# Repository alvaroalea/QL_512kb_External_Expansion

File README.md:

# SINCLAIR QL 512kB External Rom Expansion

(C) 2022 Alvaro Alea Fernandez

License under: CERN Open Hardware Licence Version 2 - Strongly Reciprocal

https://ohwr.org/cern_ohl_s_v2.txt

This is based on the work of McLeod Ideafix, Jose Leandro, Zerover and tcat between others. 

This board will provide up to 512kB aditional of static RAM (fast-ram) to the sinclair QL.

Two board can be stacked to got a maximun of 898Kb of Memory. (same as Miracle's Trump Card)

Be aware you can not have 2 memory expansion in same area (Jose Leandro's QBide, Trump Card, etc...)

Provide a expansion conector to allow conect aditional interfaces.

There area available 4 configuration trough solder jumpers in the PCB.
* 512kB - This is the standar 512kB expansion for any QL
* 256kB - This is for use as a second expansion, use the full QL space for a maximun of 898kB, be aware that this is incompatible with a lot of expansion card, so use with caution (Any expansion card that do not use jumper for configuration will be incompatible).
* 192kB - Similar to 256kB provide aditional space for expansion cards correctly configured.
* 128kB - Similar to 256kB provide aditional space for expansion cards correctly configured.

Be aware that the configuration of 128Kb can not be installed alone.
For be able to use 128kB, for a total of 768kB, is mandatory to have an aditional expansion card that put ROM in address E00000h, in other case the QL ROM will hang indicating RAM malfunction, because a weired overlap of the internal 128kB with this external 128kB.

https://www.instagram.com/p/CZWfWcUM5mx/

In the GAL folder there is the source code to be compiled with GALasm that you can found here: https://github.com/daveho/GALasm

## Mini Trump Card Compatibility

I have done a version of the trump card disk interface here: https://github.com/alvaroalea/QL_MiniTrump3 , this interface do not
provide memory like the original one. You can combine two of this card and the minitrump to got the same of the original trump card.

You should conect the 512Kb Card to the QL, the MiniTrump Card to the 512Kb, and the +256Kb card to the Mini Trump, and in this board
yo need to change the solder jumper (JP1) to 2-3 to allow the Minitrump card to coordinate with the second memory card.

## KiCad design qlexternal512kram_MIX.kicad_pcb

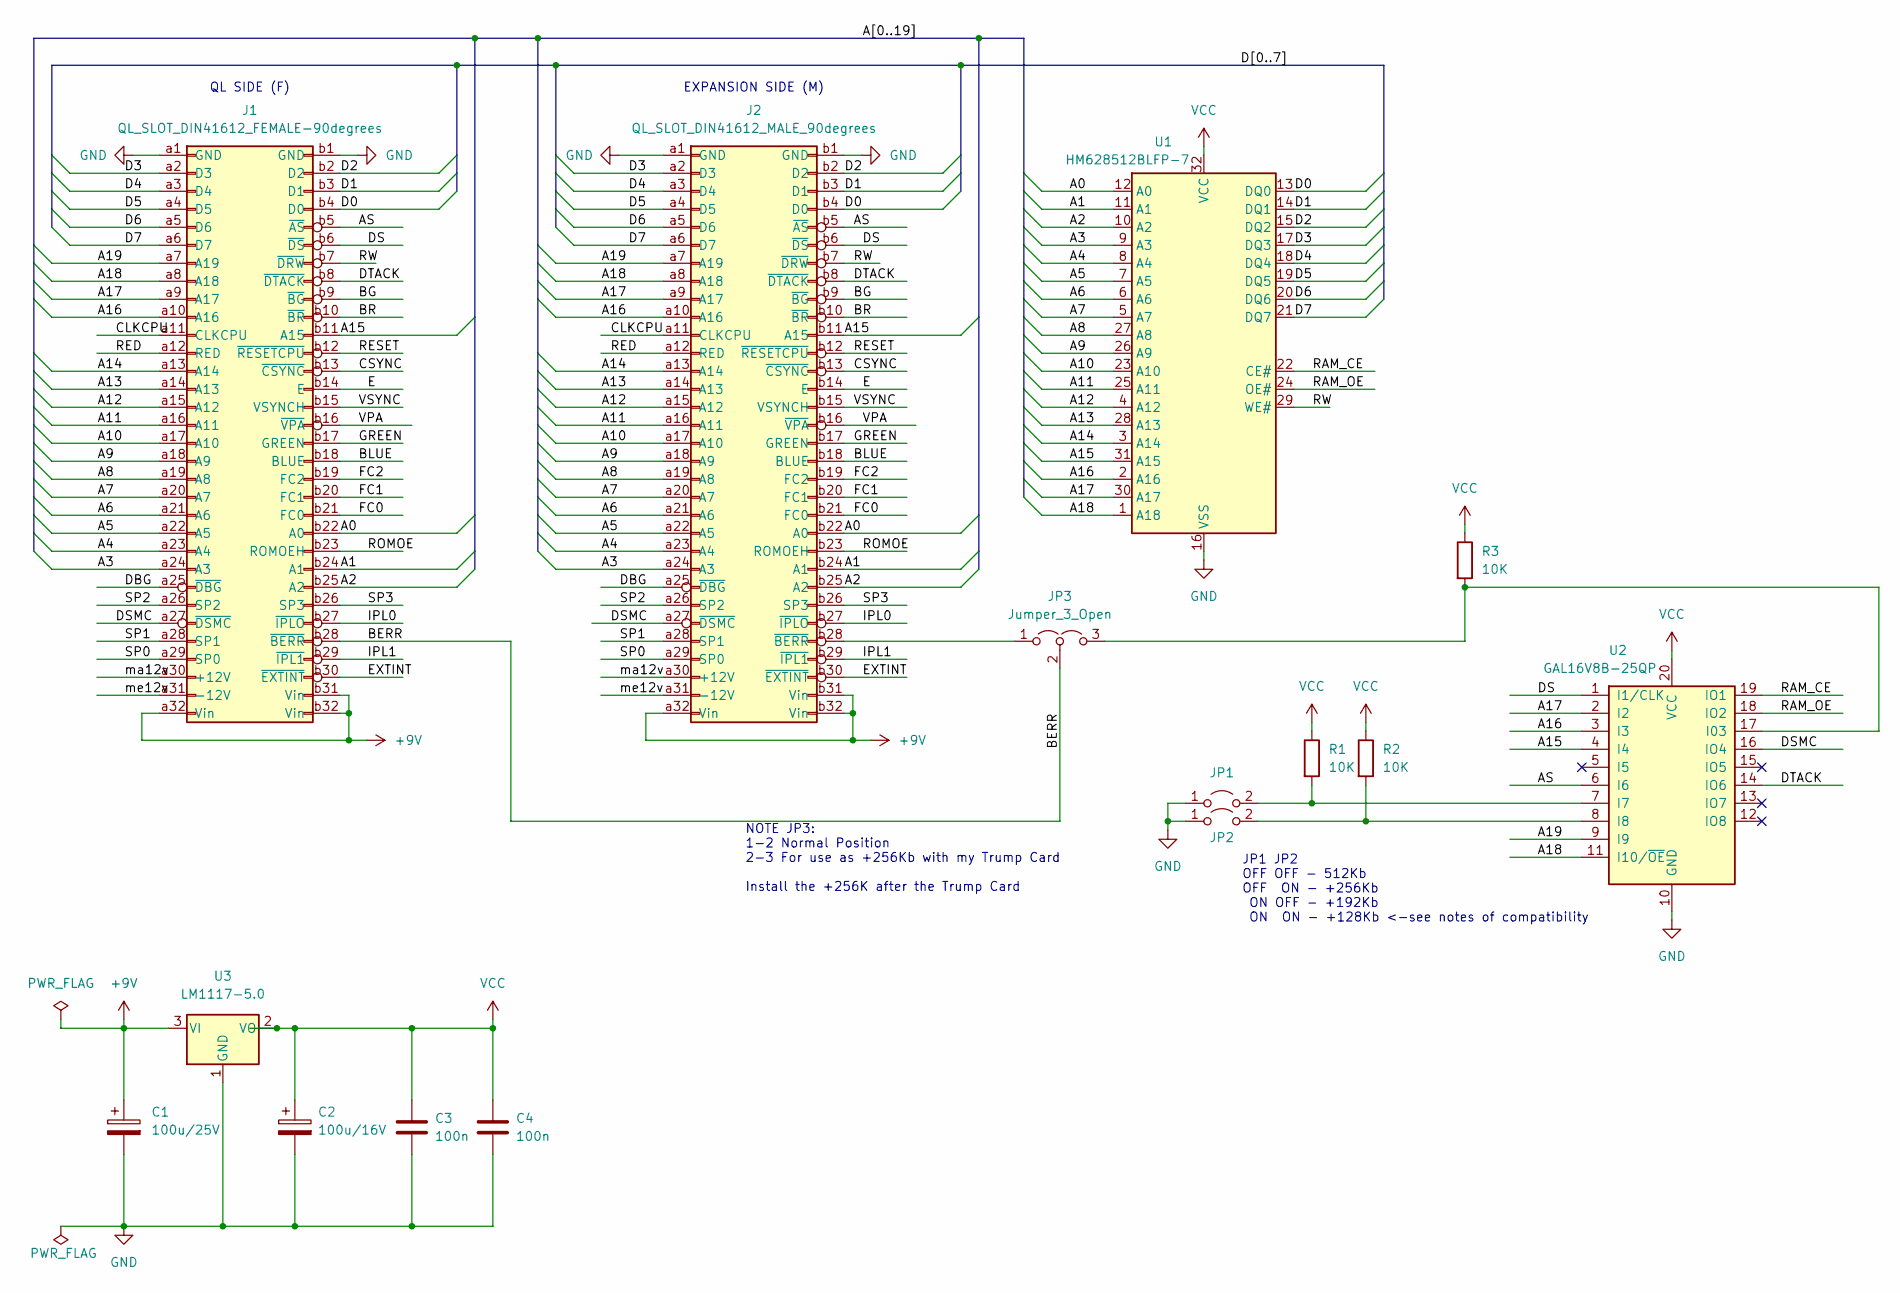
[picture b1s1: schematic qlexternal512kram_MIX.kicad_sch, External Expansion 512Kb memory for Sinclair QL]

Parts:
C1: 100u/25V; CP_Elec_6.3x5.4
C2: 100u/16V; CP_Elec_6.3x5.4
C3, C4: 100n; C_1206_3216Metric_Pad1.33x1.80mm_HandSolder
J1: QL_SLOT_DIN41612_FEMALE-90degrees; DIN41612_B_2x32_Female_Horizontal_THT
J2: QL_SLOT_DIN41612_MALE_90degrees; DIN41612_B_2x32_Male_Horizontal_THT
JP1, JP2: Jumper_2_Open; SolderJumper-2_P1.3mm_Open_Pad1.0x1.5mm
JP3: Jumper_3_Open; SolderJumper-3_P1.3mm_Open_Pad1.0x1.5mm
R1, R2, R3: 10K; R_1206_3216Metric_Pad1.30x1.75mm_HandSolder
U1: HM628512BLFP-7; SSOP-32_11.305x20.495mm_P1.27mm
U2: GAL16V8B-25QP; DIP-20_W7.62mm_LongPads
U3: LM1117-5.0; SOT-223-3_TabPin2

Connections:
+9V: C1.1, J1.a32 (Vin), J1.b31 (Vin), J1.b32 (Vin), J2.a32 (Vin), J2.b31 (Vin), J2.b32 (Vin), U3.3 (VI)
/A0: J1.b22 (A0), J2.b22 (A0), U1.12 (A0)
/A1: J1.b24 (A1), J2.b24 (A1), U1.11 (A1)
/A2: J1.b25 (A2), J2.b25 (A2), U1.10 (A2)
/A3: J1.a24 (A3), J2.a24 (A3), U1.9 (A3)
/A4: J1.a23 (A4), J2.a23 (A4), U1.8 (A4)
/A5: J1.a22 (A5), J2.a22 (A5), U1.7 (A5)
/A6: J1.a21 (A6), J2.a21 (A6), U1.6 (A6)
/A7: J1.a20 (A7), J2.a20 (A7), U1.5 (A7)
/A8: J1.a19 (A8), J2.a19 (A8), U1.27 (A8)
/A9: J1.a18 (A9), J2.a18 (A9), U1.26 (A9)
/A10: J1.a17 (A10), J2.a17 (A10), U1.23 (A10)
/A11: J1.a16 (A11), J2.a16 (A11), U1.25 (A11)
/A12: J1.a15 (A12), J2.a15 (A12), U1.4 (A12)
/A13: J1.a14 (A13), J2.a14 (A13), U1.28 (A13)
/A14: J1.a13 (A14), J2.a13 (A14), U1.3 (A14)
/A15: J1.b11 (A15), J2.b11 (A15), U1.31 (A15), U2.4 (I4)
/A16: J1.a10 (A16), J2.a10 (A16), U1.2 (A16), U2.3 (I3)
/A17: J1.a9 (A17), J2.a9 (A17), U1.30 (A17), U2.2 (I2)
/A18: J1.a8 (A18), J2.a8 (A18), U1.1 (A18), U2.11 (I10/~OE)
/A19: J1.a7 (A19), J2.a7 (A19), U2.9 (I9)
/AS: J1.b5 (~AS), J2.b5 (~AS), U2.6 (I6)
/BERR: J1.b28 (~BERR), JP3.2 (C)
/BG: J1.b9 (~BG), J2.b9 (~BG)
/BLUE: J1.b18 (BLUE), J2.b18 (BLUE)
/BR: J1.b10 (~BR), J2.b10 (~BR)
/CLKCPU: J1.a11 (CLKCPU), J2.a11 (CLKCPU)
/CSYNC: J1.b13 (~CSYNC), J2.b13 (~CSYNC)
/D0: J1.b4 (D0), J2.b4 (D0), U1.13 (DQ0)
/D1: J1.b3 (D1), J2.b3 (D1), U1.14 (DQ1)
/D2: J1.b2 (D2), J2.b2 (D2), U1.15 (DQ2)
/D3: J1.a2 (D3), J2.a2 (D3), U1.17 (DQ3)
/D4: J1.a3 (D4), J2.a3 (D4), U1.18 (DQ4)
/D5: J1.a4 (D5), J2.a4 (D5), U1.19 (DQ5)
/D6: J1.a5 (D6), J2.a5 (D6), U1.20 (DQ6)
/D7: J1.a6 (D7), J2.a6 (D7), U1.21 (DQ7)
/DBG: J1.a25 (~DBG), J2.a25 (~DBG)
/DS: J1.b6 (~DS), J2.b6 (~DS), U2.1 (I1/CLK)
/DSMC: J1.a27 (~DSMC), J2.a27 (~DSMC), U2.16 (IO4)
/DTACK: J1.b8 (~DTACK), J2.b8 (~DTACK), U2.14 (IO6)
/E: J1.b14 (E), J2.b14 (E)
/EXTINT: J1.b30 (~EXTINT), J2.b30 (~EXTINT)
/FC0: J1.b21 (FC0), J2.b21 (FC0)
/FC1: J1.b20 (FC1), J2.b20 (FC1)
/FC2: J1.b19 (FC2), J2.b19 (FC2)
/GREEN: J1.b17 (GREEN), J2.b17 (GREEN)
/IPL0: J1.b27 (~IPLO), J2.b27 (~IPLO)
/IPL1: J1.b29 (~IPL1), J2.b29 (~IPL1)
/RAM_CE: U1.22 (CE#), U2.19 (IO1)
/RAM_OE: U1.24 (OE#), U2.18 (IO2)
/RED: J1.a12 (RED), J2.a12 (RED)
/RESET: J1.b12 (~RESETCPU), J2.b12 (~RESETCPU)
/ROMOE: J1.b23 (ROMOEH), J2.b23 (ROMOEH)
/RW: J1.b7 (~DRW), J2.b7 (~DRW), U1.29 (WE#)
/SP0: J1.a29 (SP0), J2.a29 (SP0)
/SP1: J1.a28 (SP1), J2.a28 (SP1)
/SP2: J1.a26 (SP2), J2.a26 (SP2)
/SP3: J1.b26 (SP3), J2.b26 (SP3)
/VPA: J1.b16 (~VPA), J2.b16 (~VPA)
/VSYNC: J1.b15 (VSYNCH), J2.b15 (VSYNCH)
/ma12v: J1.a30 (+12V), J2.a30 (+12V)
/me12v: J1.a31 (-12V), J2.a31 (-12V)
GND: C1.2, C2.2, C3.2, C4.2, J1.a1 (GND), J1.b1 (GND), J2.a1 (GND), J2.b1 (GND), JP1.1 (A), JP2.1 (A), U1.16 (VSS), U2.10 (GND), U3.1 (GND)
unnamed: J2.b28 (~BERR), JP3.1 (A)
unnamed: JP1.2 (B), R1.2, U2.7 (I7)
unnamed: JP2.2 (B), R2.2, U2.8 (I8)
unnamed: JP3.3 (B), R3.2, U2.17 (I03)
VCC: C2.1, C3.1, C4.1, R1.1, R2.1, R3.1, U1.32 (VCC), U2.20 (VCC), U3.2 (VO)

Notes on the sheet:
NOTE JP3: 1-2 Normal Position 2-3 For use as +256Kb with my Trump Card Install the +256K after the Trump Card
EXPANSION SIDE (M)
JP1 JP2 OFF OFF - 512Kb OFF ON - +256Kb ON OFF - +192Kb ON ON - +128Kb <-see notes of compatibility
QL SIDE (F)

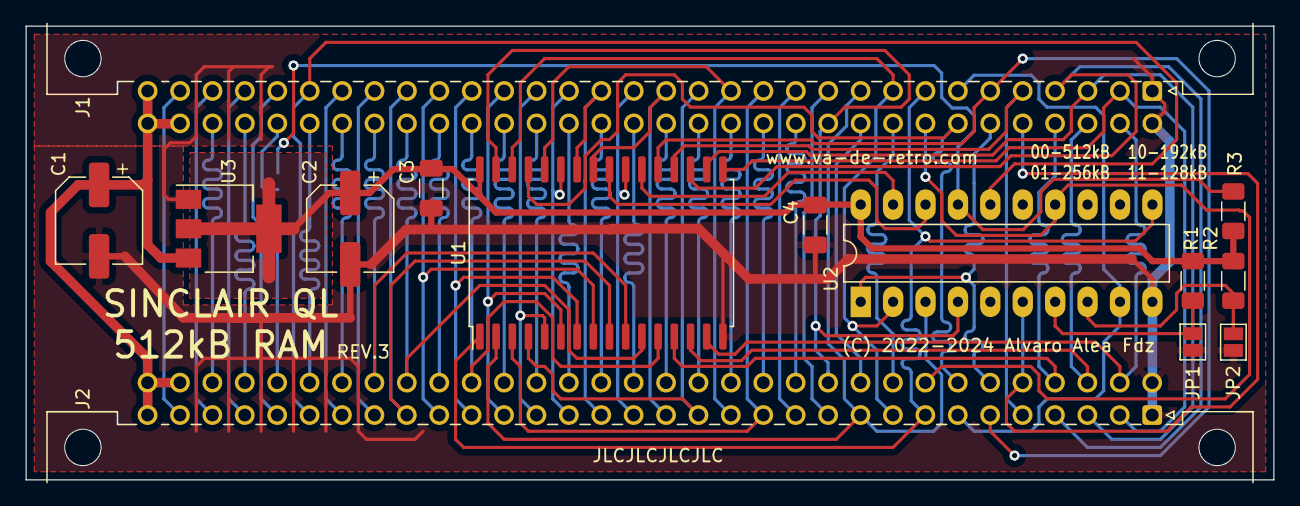
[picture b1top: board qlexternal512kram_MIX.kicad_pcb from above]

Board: 2 copper layers, 97.8 x 35.6 mm, 15 parts (1 on the bottom side), 68 nets.

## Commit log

2022-02-13 Initial
2022-02-14 Fix reference for IC
2022-06-18 Typo
2022-07-15 Updated info
2022-07-15 Update info
2022-07-21 fix bank jumpers not working
2023-12-26 Update QL Conector
2023-12-26 update gerber zip
2024-11-08 Add compatibility with MiniTrump Card, and moved GAL to galasm
2024-11-22 minor typos
2024-12-06 typo in skillscreen

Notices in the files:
qlexternal512kram_MIX.kicad_pcb:
(C) 2022 Alvaro Alea Fdz.
Under License
Licensed under Cern OHL-S
(C) 2022-2024 Alvaro Alea Fdz
